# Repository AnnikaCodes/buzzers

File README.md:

# ABACUS: Annika's Buzzers for Ascertaining Competitive Unique Signals
a lower-cost buzzer system for quizbowl competitions

the 3D models were based on https://www.thingiverse.com/thing:12686 and https://www.thingiverse.com/thing:1432052 and https://www.thingiverse.com/thing:1155457

check out [the 'real' website for these!](https://worldbrightening.net/buzzers/)

I don't yet have detailed directions for building it, but you should definitely:
- get a PCB; you can fabricate [these files](https://github.com/AnnikaCodes/buzzers/tree/main/buzzer-pcb), or I'll send you one (almost certainly for cheaper and potentially for free) if you [contact me](mailto:annika@worldbrightening.net)
- buy [stuff from DigiKey](https://www.digikey.com/en/mylists/list/PRWZMR6ARL) (I don't know if this list is complete... you also will definitely need a [speaker](https://www.amazon.com/MakerHawk-Full-Range-Advertising-Connector-Separating/dp/B07GJ4GH67) and some resistors and please, like, [email me about this](mailto:annika@worldbrightening.net) or Discord me or something if you are going to build this! I will help you!)
- print 10 of the [3D models for the buzzers](https://github.com/AnnikaCodes/buzzers/blob/main/3Dmodels/buzzer2.stl) and one of the [3D models for the case](https://github.com/AnnikaCodes/buzzers/blob/main/buzzer-case.stl) (which I still need to move the hole for the cord down to make it actually fit....)
- cut in half your 4p4c cables, push the wire ends through, solder the pushbutton switch to the right wires (this should be RED and GREEN but maybe double check with a multimeter?) and the LED positive lead to black and ground lead to yellow. 
    - be sure to use electrical tape or heatshrink to make it not short itself out!
- glue the buzzers together, and maybe put some superglue around the bottom to stop people from yanking the cord out
- solder all the jacks to the PCB and resistors to limit the current to the LEDs to the board --- whatever you need to reduce 3.3V to a reasonable amount of current given the diode drop of the LED you're using, but I used 50-60 Ohms and mine haven't broken yet.
- solder the Raspberry Pi to the board, maybe with headers if desired
- put red + green LEDs and a switch into the case with wires attached, then attach the wires either directly to the board with solder in the appropriate places, or through headers
- glue the switch into the case, and close the case
- download the software and you're off!

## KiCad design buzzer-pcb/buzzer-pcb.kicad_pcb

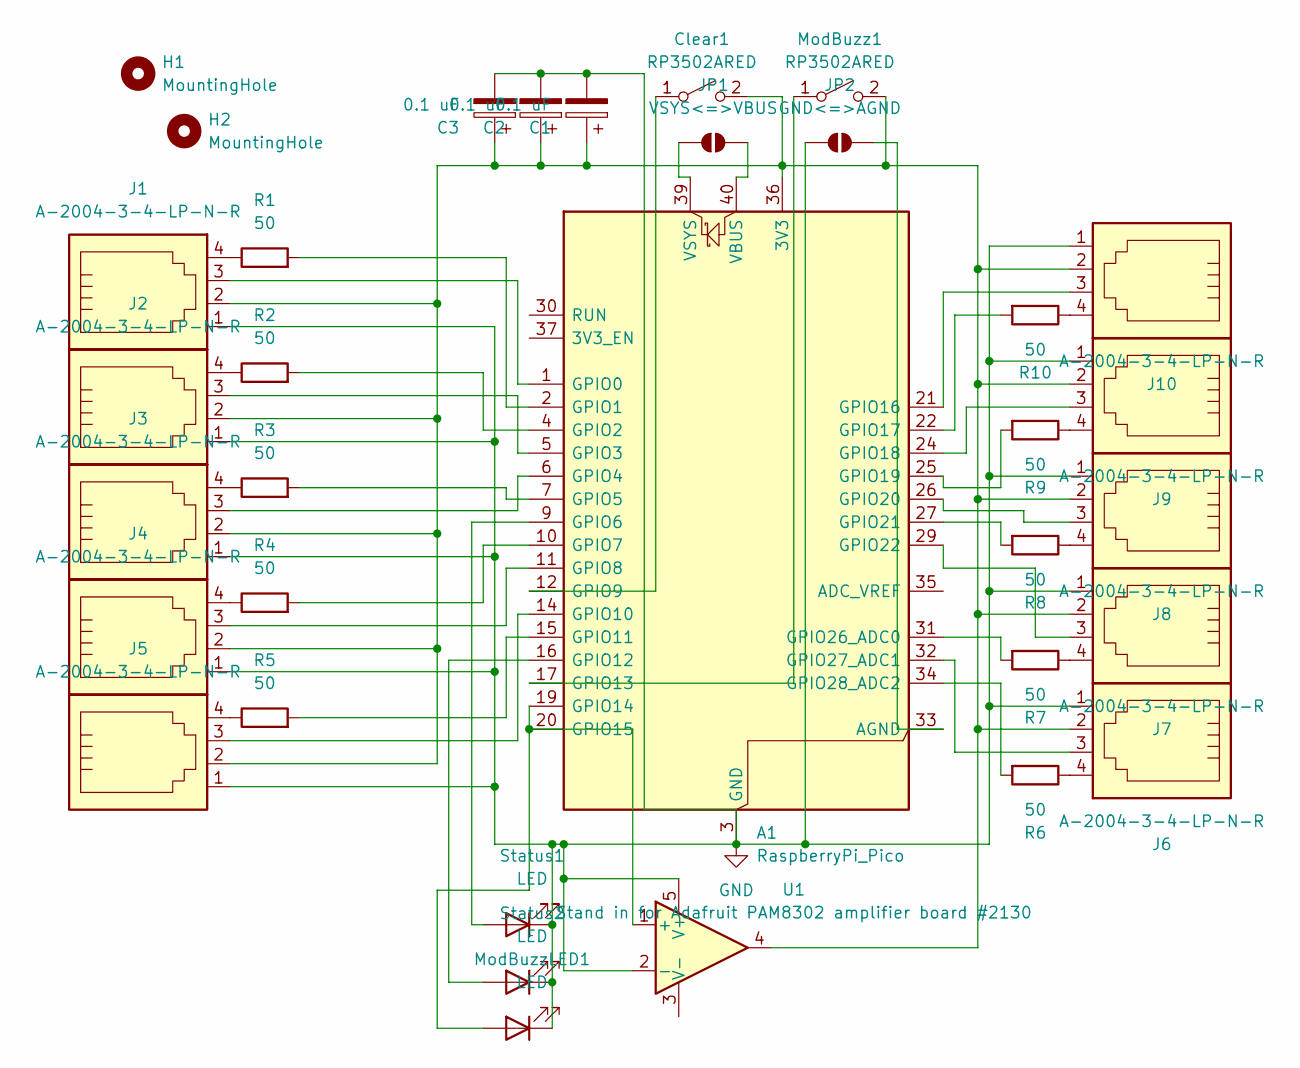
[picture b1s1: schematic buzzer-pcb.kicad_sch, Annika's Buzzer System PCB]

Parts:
A1: RaspberryPi_Pico; RaspberryPi_Pico_Common_THT
C1, C2, C3: 0.1 uF; XTAL_ZTA-2.44MG
Clear1: RP3502ARED; SW_CW_GPTS203211B
H1, H2: MountingHole; MountingHole_3.2mm_M3
J1, J2, J3, J4, J5, J6, J7, J8, J9, J10: A-2004-3-4-LP-N-R; Jack for Buzzers
JP1: VSYS<=>VBUS; SolderJumper-2_P1.3mm_Bridged_Pad1.0x1.5mm
JP2: GND<=>AGND; SolderJumper-2_P1.3mm_Bridged_Pad1.0x1.5mm
ModBuzz1: RP3502ARED; SW_CW_GPTS203211B
ModBuzzLED1: LED; LED_D5.0mm
R1, R2, R3, R4, R5, R6, R7, R8, R9, R10: 50; R_Axial_DIN0414_L11.9mm_D4.5mm_P15.24mm_Horizontal
Status1, Status2: LED; LED_D5.0mm
U1: Stand in for Adafruit PAM8302 amplifier board #21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; TO-264-5_Horizontal_TabDown

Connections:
GND: A1.3 (GND), A1.8 (GND), A1.13 (GND), A1.18 (GND), A1.23 (GND), A1.28 (GND), A1.38 (GND), C1.2, C2.2, C3.2, J1.1, J2.1, J3.1, J4.1, J5.1, J6.1, J7.1, J8.1, J9.1, J10.1, JP2.1 (A), ModBuzzLED1.1 (K), Status1.1 (K), Status2.1 (K), U1.2 (-), U1.5 (V+)
unnamed: A1.36 (3V3), C1.1, C2.1, C3.1, Clear1.2 (B), J1.2, J2.2, J3.2, J4.2, J5.2, J6.2, J7.2, J8.2, J9.2, J10.2, ModBuzz1.2 (B), U1.4
unnamed: A1.33 (AGND), JP2.2 (B)
unnamed: A1.1 (GPIO0), J1.3
unnamed: A1.2 (GPIO1), R1.2
unnamed: A1.4 (GPIO2), R2.2
unnamed: A1.5 (GPIO3), J2.3
unnamed: A1.6 (GPIO4), J3.3
unnamed: A1.7 (GPIO5), R3.2
unnamed: A1.9 (GPIO6), Status1.2 (A)
unnamed: A1.10 (GPIO7), R4.2
unnamed: A1.11 (GPIO8), J4.3
unnamed: A1.12 (GPIO9), Clear1.1 (A)
unnamed: A1.14 (GPIO10), J5.3
unnamed: A1.15 (GPIO11), R5.2
unnamed: A1.16 (GPIO12), Status2.2 (A)
unnamed: A1.17 (GPIO13), ModBuzz1.1 (A)
unnamed: A1.19 (GPIO14), A1.20 (GPIO15), ModBuzzLED1.2 (A), U1.1 (+)
unnamed: A1.21 (GPIO16), J10.3
unnamed: A1.22 (GPIO17), R10.2
unnamed: A1.24 (GPIO18), J9.3
unnamed: A1.25 (GPIO19), R9.2
unnamed: A1.26 (GPIO20), J8.3
unnamed: A1.27 (GPIO21), R8.2
unnamed: A1.29 (GPIO22), J7.3
unnamed: A1.31 (GPIO26_ADC0), R7.2
unnamed: A1.32 (GPIO27_ADC1), J6.3
unnamed: A1.34 (GPIO28_ADC2), R6.2
unnamed: A1.40 (VBUS), JP1.2 (B)
unnamed: A1.39 (VSYS), JP1.1 (A)
unnamed: J1.4, R1.1
unnamed: J2.4, R2.1
unnamed: J3.4, R3.1
unnamed: J4.4, R4.1
unnamed: J5.4, R5.1
unnamed: J6.4, R6.1
unnamed: J7.4, R7.1
unnamed: J8.4, R8.1
unnamed: J9.4, R9.1
unnamed: J10.4, R10.1

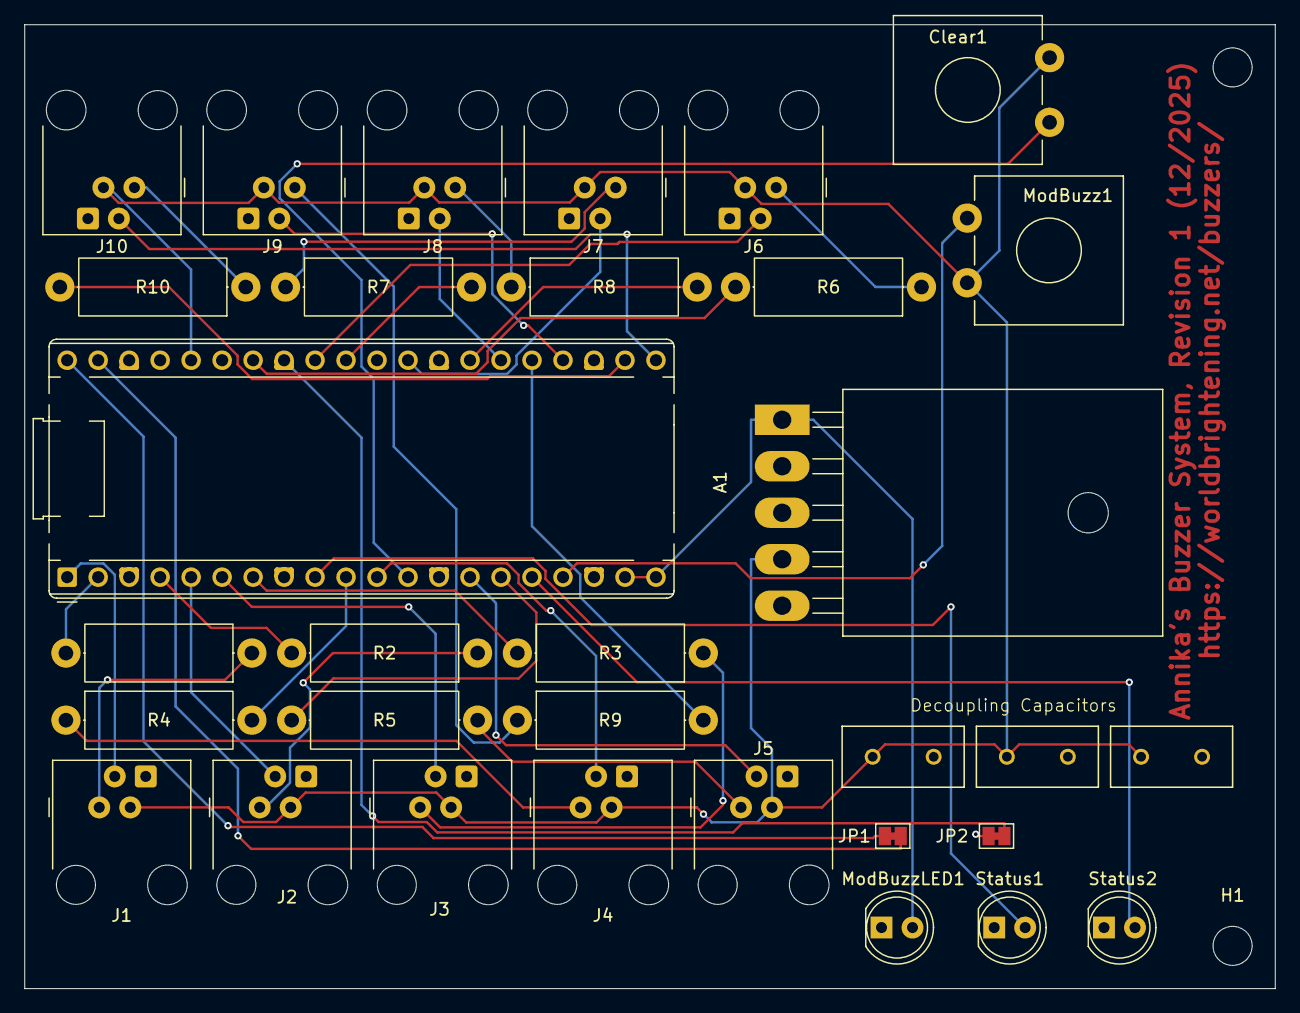
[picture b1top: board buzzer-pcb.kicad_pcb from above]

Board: 2 copper layers, 102.5 x 79.0 mm, 34 parts (0 on the bottom side), 40 nets.

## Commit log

2025-10-28 Add 3D model for buzzer
2025-10-29 Notes
2025-10-29 Buzzer model: Make cable exhaust small
2025-10-29 3D model updates
2025-10-29 Add Digikey LED model
2025-11-09 yeah
2025-12-23 Some attempts at protocol stuff
2025-12-24 Begin writing serial-based UI
2025-12-25 Protocol/communication is now working!
2025-12-26 UI for received messages
2025-12-26 Bux fixes
2025-12-26 Run `cargo fmt`
2025-12-28 PCB design
2026-02-03 Bump bytes from 1.11.0 to 1.11.1 in /buzzer-ui
    Bumps [bytes](https://github.com/tokio-rs/bytes) from 1.11.0 to 1.11.1.
    - [Release notes](https://github.com/tokio-rs/bytes/releases)
    - [Changelog](https://github.com/tokio-rs/bytes/blob/master/CHANGELOG.md)
    - [Commits](https://github.com/tokio-rs/bytes/compare/v1.11.0...v1.11.1)
    ---
    updated-dependencies:
2026-02-07 Attempt installability + icon
2026-02-07 Add some details
2026-02-07 release: version 0.1.0
2026-02-07 Move Rust code outside of folder
2026-02-07 Bump bytes from 1.11.0 to 1.11.1
    Bumps [bytes](https://github.com/tokio-rs/bytes) from 1.11.0 to 1.11.1.
    - [Release notes](https://github.com/tokio-rs/bytes/releases)
    - [Changelog](https://github.com/tokio-rs/bytes/blob/master/CHANGELOG.md)
    - [Commits](https://github.com/tokio-rs/bytes/compare/v1.11.0...v1.11.1)
    ---
    updated-dependencies:
2026-02-07 Fix action for Linux
2026-02-10 Start work log for UCI buzzers
2026-02-11 work log
2026-02-16 Update buzzer case model
